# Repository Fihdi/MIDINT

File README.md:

# 6hp MIDI Interface (work in progress)

MIDINT is an eight channel MIDI interface in 6hp. Take a standard DIN-5 MIDI cable connected to your favorite DAW or MIDI gear and control up to eight Gate, Trigger and CV channels. Trimmers on the back of the module allow for precise V/Oct tuning. The CV outputs can thus control oscillators and filters without the need for an external quantizer.

Selecting a channel with the "SELECT" encoder and pressing it will switch it between a trigger or gate output.

# Features

- 4 Gate or Trigger outputs
- 4 CV outputs (Can also be used as Gate or Trigger outputs)
- Extension of up to three modules.

# Extension 

Its possible to daisy-chain up to three extension modules to one main module and expand your interface system to a maximum of 32 Gate/Trigger/CV channels. To connect extension module(s) to a main module:

WARNING: Do NOT connect main modules together!

- Turn your modular synthesizer off
- Take an extension module(s) and change the jumper from "MAIN" to "EXT".
- Add jumpers to "EXT1" and "EXT2" to configure the MIDI channels (see table below)
- Connect the extension module(s) to a main module or another extension module in the chain with a wire underneath the power connector.
- Connect each module(s) to power
- Turn your modular synthesizer on

By connecting a MIDI cable into the main module the MIDI data is shared between all modules. The extension modules are addressed by the jumper settings EXT1 and EXT2:

//TODO: Add address table

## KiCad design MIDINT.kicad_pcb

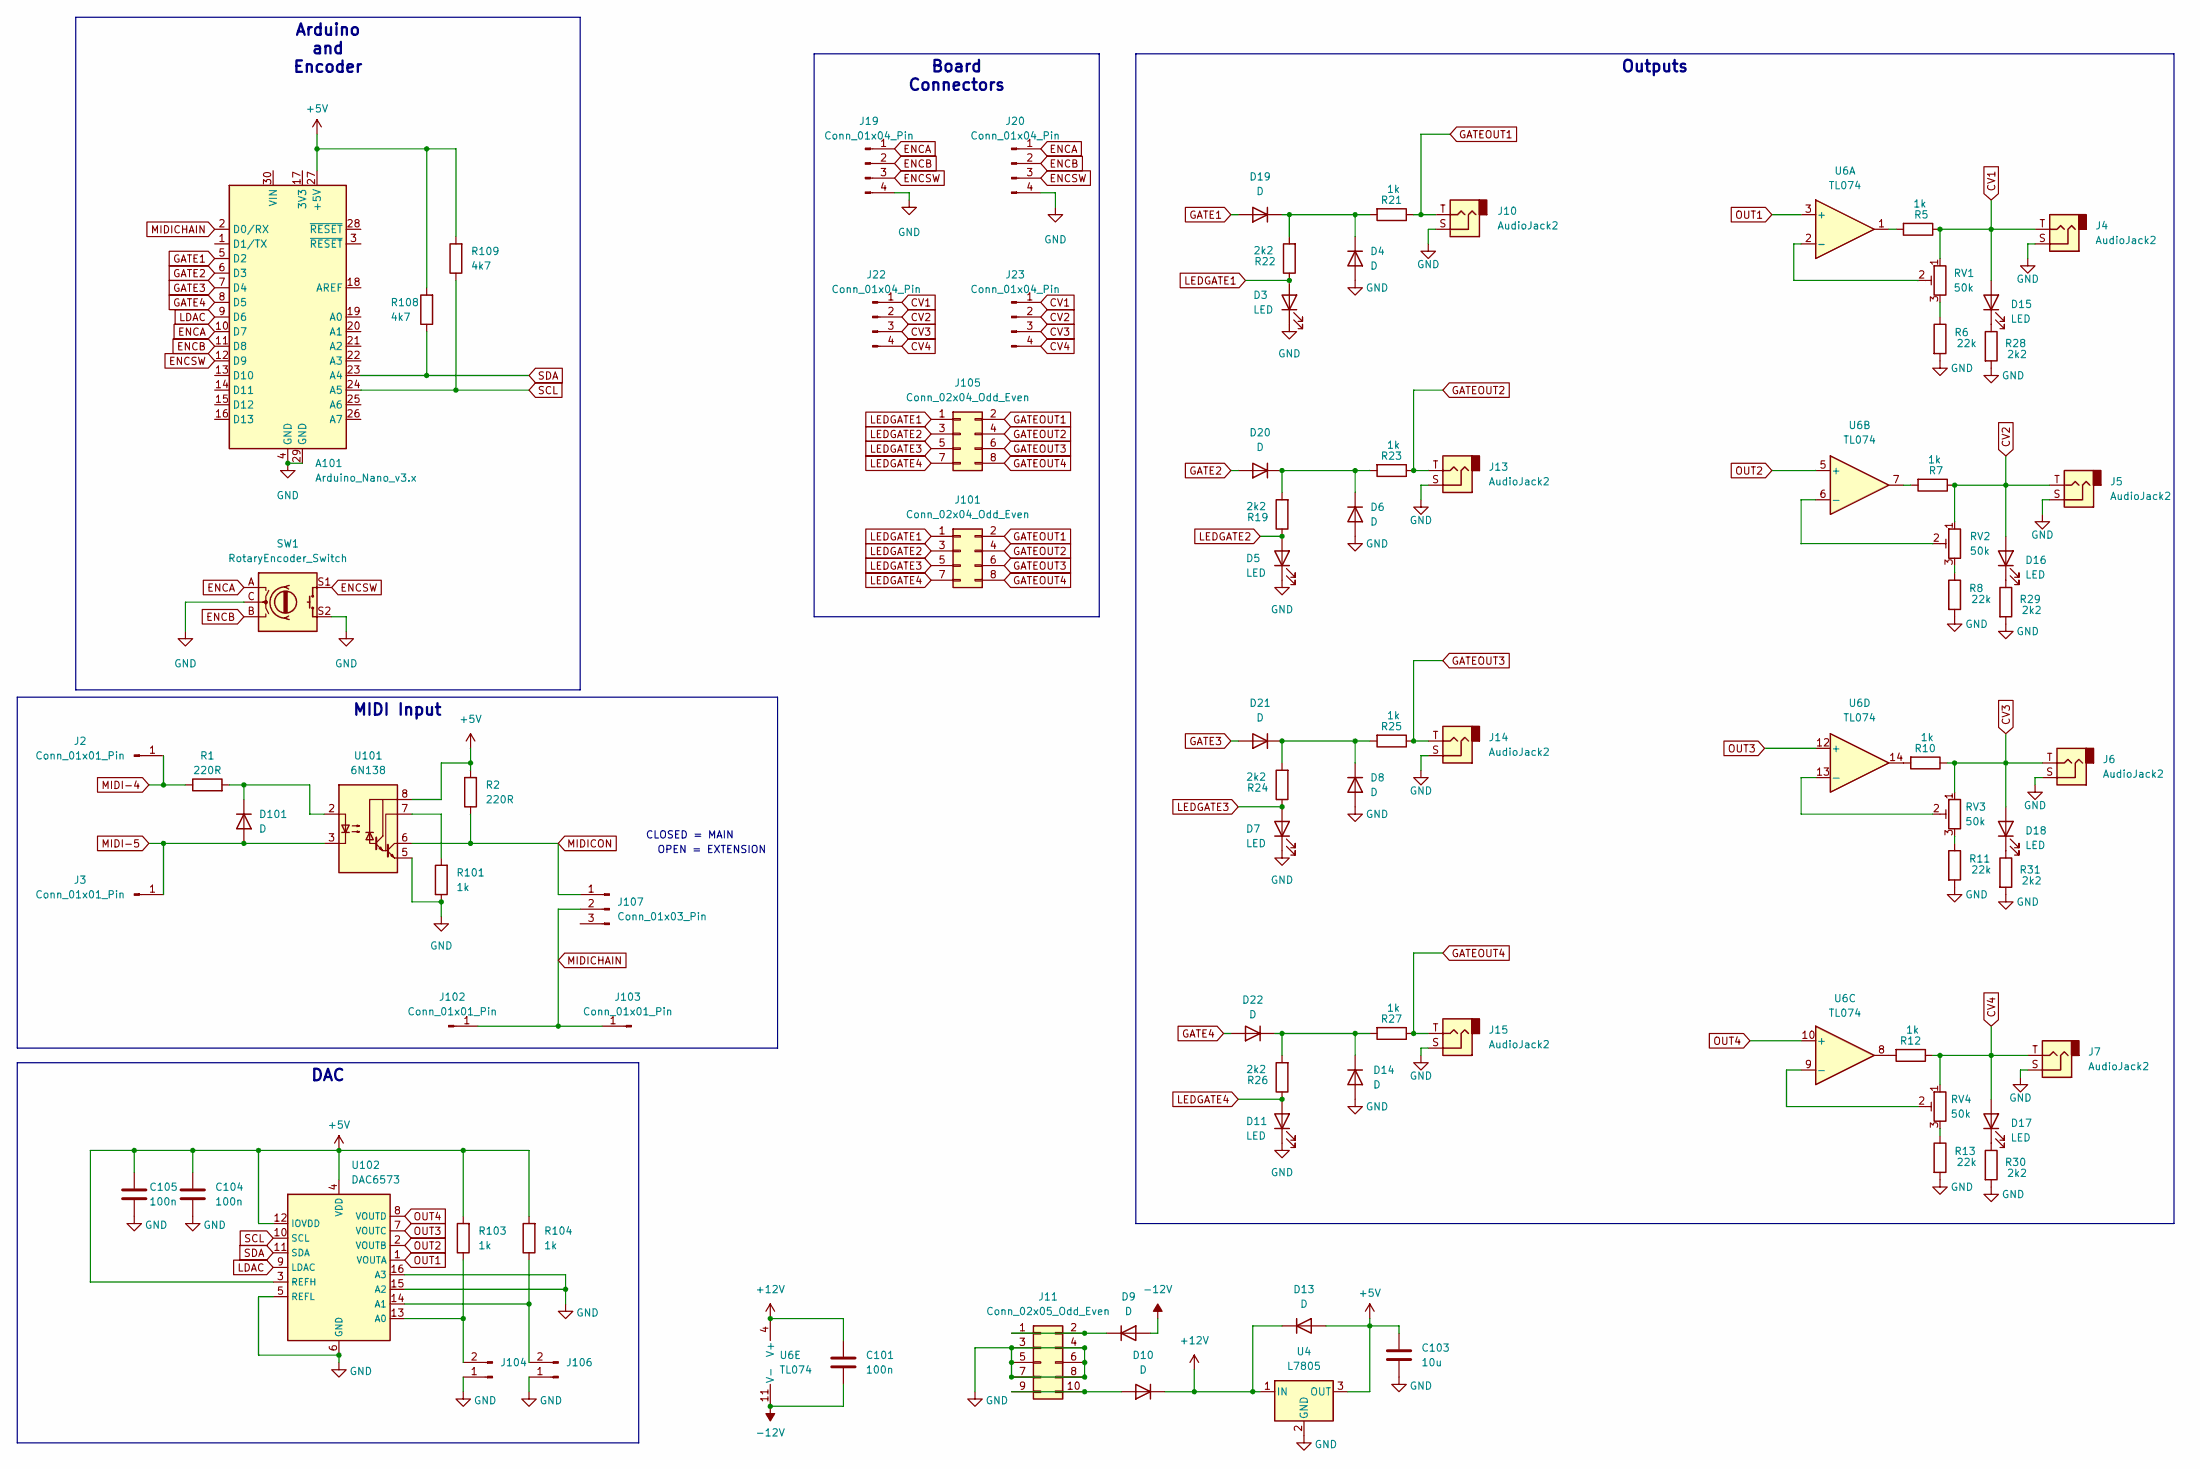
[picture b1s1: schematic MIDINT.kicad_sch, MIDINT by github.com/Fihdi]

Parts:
A101: Arduino_Nano_v3.x; Arduino_Nano
C101, C104, C105: 100n; C_1206_3216Metric
C103: 10u; C_1206_3216Metric
D3, D5, D7, D11, D15, D16, D17, D18: LED; LED_D3.0mm
D4, D6, D8, D9, D10, D13, D14, D19, D20, D21, D22, D101: D; D_SOD-323_HandSoldering
J2, J3, J102, J103: Conn_01x01_Pin; PinHeader_1x01_P2.54mm_Vertical
J4, J5, J6, J7, J10, J13, J14, J15: AudioJack2; MonoTRS
J11: Conn_02x05_Odd_Even; IDC-Header_2x05_P2.54mm_Vertical
J19, J20, J22, J23: Conn_01x04_Pin; PinHeader_1x04_P2.54mm_Vertical
J101, J105: Conn_02x04_Odd_Even; PinHeader_2x04_P2.54mm_Vertical
J104, J106: Conn_01x02_Pin; PinHeader_1x02_P2.54mm_Vertical
J107: Conn_01x03_Pin; PinHeader_1x03_P2.54mm_Vertical
R1, R2: 220R; R_1206_3216Metric
R5, R7, R10, R12, R21, R23, R25, R27, R101, R103, R104: 1k; R_1206_3216Metric
R6, R8, R11, R13: 22k; R_1206_3216Metric
R19, R22, R24, R26, R28, R29, R30, R31: 2k2; R_1206_3216Metric
R108, R109: 4k7; R_1206_3216Metric
RV1, RV2, RV3, RV4: 50k; Potentiometer_Bourns_3296W_Vertical
SW1: RotaryEncoder_Switch; RotaryEncoder_Alps_EC12E-Switch_Vertical_H20mm
U4: L7805; SOT-223
U6: TL074; SOIC-14_3.9x8.7mm_P1.27mm
U101: 6N138; DIP-8_W7.62mm
U102: DAC6573; TSSOP-16_4.4x5mm_P0.65mm

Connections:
+5V: A101.27 (+5V), C103.1, C104.1, C105.1, D13.2 (A), R2.2, R103.2, R104.2, R108.2, R109.2, U4.3 (OUT), U101.8 (VCC), U102.3 (REFH), U102.4 (VDD), U102.12 (IOVDD)
+12V: C101.1, D10.1 (K), D13.1 (K), U4.1 (IN), U6.4 (V+)
-12V: C101.2, D9.2 (A), U6.11 (V-)
CV1: D15.2 (A), J4.T, J22.1, J23.1, R5.1, RV1.1
CV2: D16.2 (A), J5.T, J22.2, J23.2, R7.1, RV2.1
CV3: D18.2 (A), J6.T, J22.3, J23.3, R10.1, RV3.1
CV4: D17.2 (A), J7.T, J22.4, J23.4, R12.1, RV4.1
ENCA: A101.10 (D7), J19.1, J20.1, SW1.A
ENCB: A101.11 (D8), J19.2, J20.2, SW1.B
ENCSW: A101.12 (D9), J19.3, J20.3, SW1.S1
GATE1: A101.5 (D2), D19.2 (A)
GATE2: A101.6 (D3), D20.2 (A)
GATE3: A101.7 (D4), D21.2 (A)
GATE4: A101.8 (D5), D22.2 (A)
GATEOUT1: J10.T, J101.2, J105.2, R21.1
GATEOUT2: J13.T, J101.4, J105.4, R23.1
GATEOUT3: J14.T, J101.6, J105.6, R25.1
GATEOUT4: J15.T, J101.8, J105.8, R27.1
GND: A101.4 (GND), A101.29 (GND), C103.2, C104.2, C105.2, D3.1 (K), D4.2 (A), D5.1 (K), D6.2 (A), D7.1 (K), D8.2 (A), D11.1 (K), D14.2 (A), J4.S, J5.S, J6.S, J7.S, J10.S, J11.3, J11.4, J11.5, J11.6, J11.7, J11.8, J13.S, J14.S, J15.S, J19.4, J20.4, J104.1, J106.1, R6.2, R8.2, R11.2, R13.2, R28.2, R29.2, R30.2, R31.2, R101.1, SW1.C, SW1.S2, U4.2 (GND), U101.5 (GND), U102.5 (REFL), U102.6 (GND), U102.15 (A2), U102.16 (A3)
LDAC: A101.9 (D6), U102.9 (LDAC)
LEDGATE1: D3.2 (A), J101.1, J105.1, R22.1
LEDGATE2: D5.2 (A), J101.3, J105.3, R19.1
LEDGATE3: D7.2 (A), J101.5, J105.5, R24.1
LEDGATE4: D11.2 (A), J101.7, J105.7, R26.1
MIDI-4: J2.1, R1.1
MIDI-5: D101.2 (A), J3.1, U101.3 (C2)
MIDICHAIN: A101.2 (D0/RX), J102.1, J103.1, J107.2
MIDICON: J107.1, R2.1, U101.6 (VO2)
unnamed: D9.1 (K), J11.1, J11.2
unnamed: D10.2 (A), J11.9, J11.10
unnamed: D14.1 (K), D22.1 (K), R26.2, R27.2
unnamed: D15.1 (K), R28.1
unnamed: D16.1 (K), R29.1
unnamed: D17.1 (K), R30.1
unnamed: D18.1 (K), R31.1
unnamed: D4.1 (K), D19.1 (K), R21.2, R22.2
unnamed: D6.1 (K), D20.1 (K), R19.2, R23.2
unnamed: D8.1 (K), D21.1 (K), R24.2, R25.2
unnamed: D101.1 (K), R1.2, U101.2 (C1)
unnamed: J104.2, R103.1, U102.13 (A0)
unnamed: J106.2, R104.1, U102.14 (A1)
unnamed: R5.2, U6.1
unnamed: R6.1, RV1.3
unnamed: R7.2, U6.7
unnamed: R8.1, RV2.3
unnamed: R10.2, U6.14
unnamed: R11.1, RV3.3
unnamed: R12.2, U6.8
unnamed: R13.1, RV4.3
unnamed: RV1.2, U6.2 (-)
unnamed: RV2.2, U6.6 (-)
unnamed: RV4.2, U6.9 (-)
unnamed: RV3.2, U6.13 (-)
unnamed: R101.2, U101.7 (VO1)
OUT1: U6.3 (+), U102.1 (VOUTA)
OUT2: U6.5 (+), U102.2 (VOUTB)
OUT3: U6.12 (+), U102.7 (VOUTC)
OUT4: U6.10 (+), U102.8 (VOUTD)
SCL: A101.24 (A5), R109.1, U102.10 (SCL)
SDA: A101.23 (A4), R108.1, U102.11 (SDA)

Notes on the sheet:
CLOSED = MAIN
OPEN = EXTENSION
MIDI Input
DAC
Board Connectors
Arduino and Encoder
Outputs

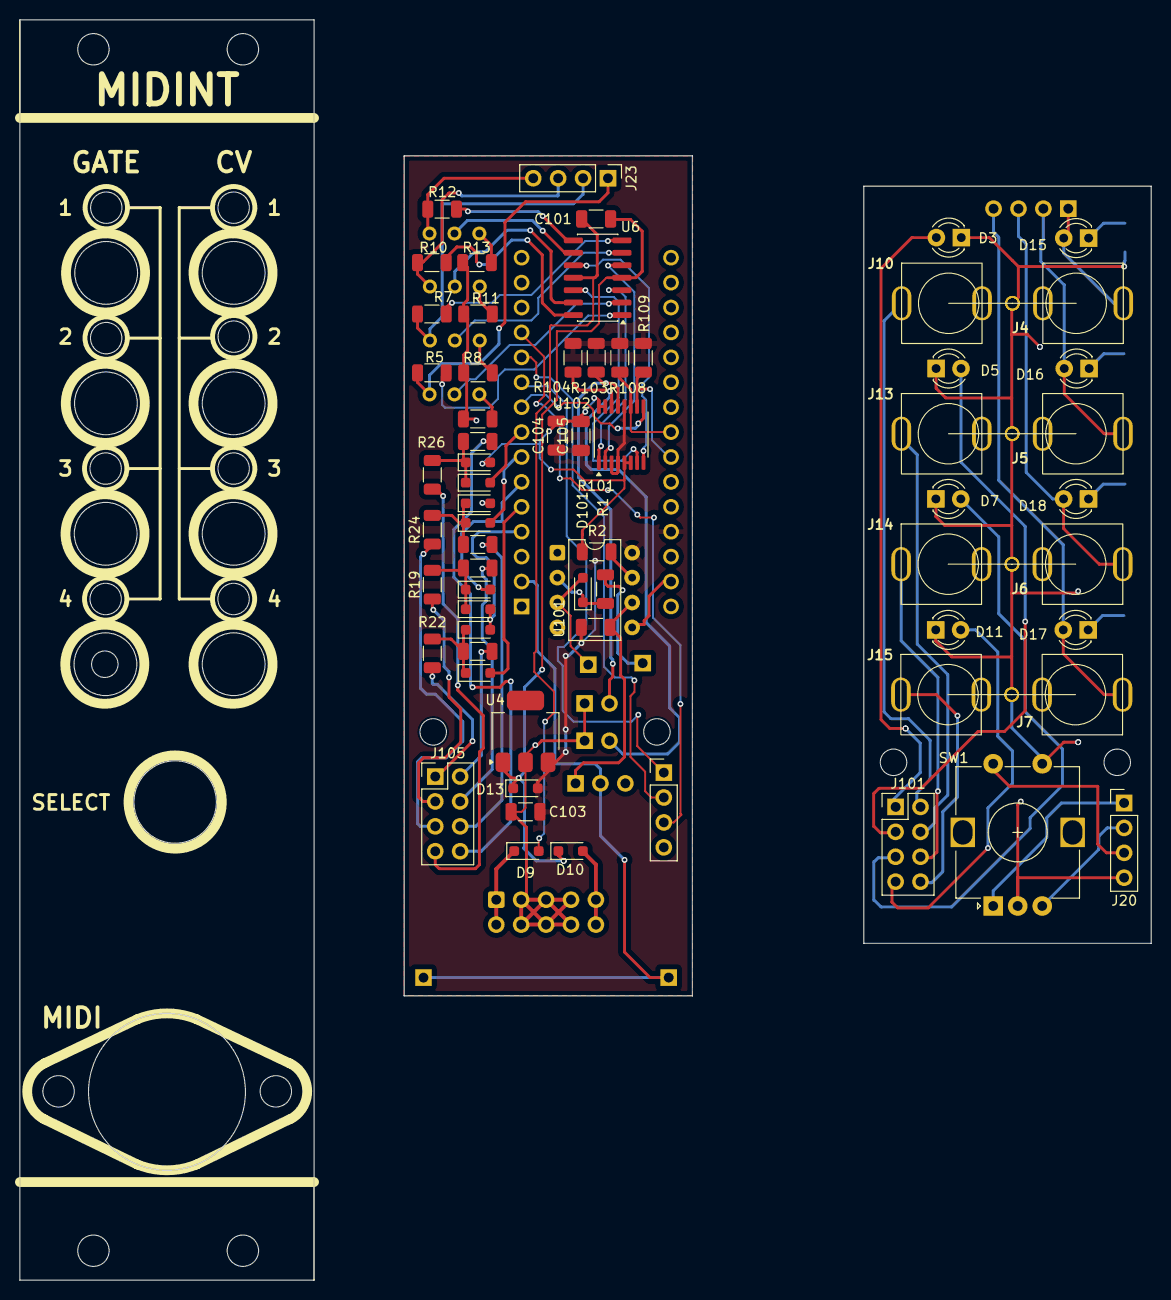
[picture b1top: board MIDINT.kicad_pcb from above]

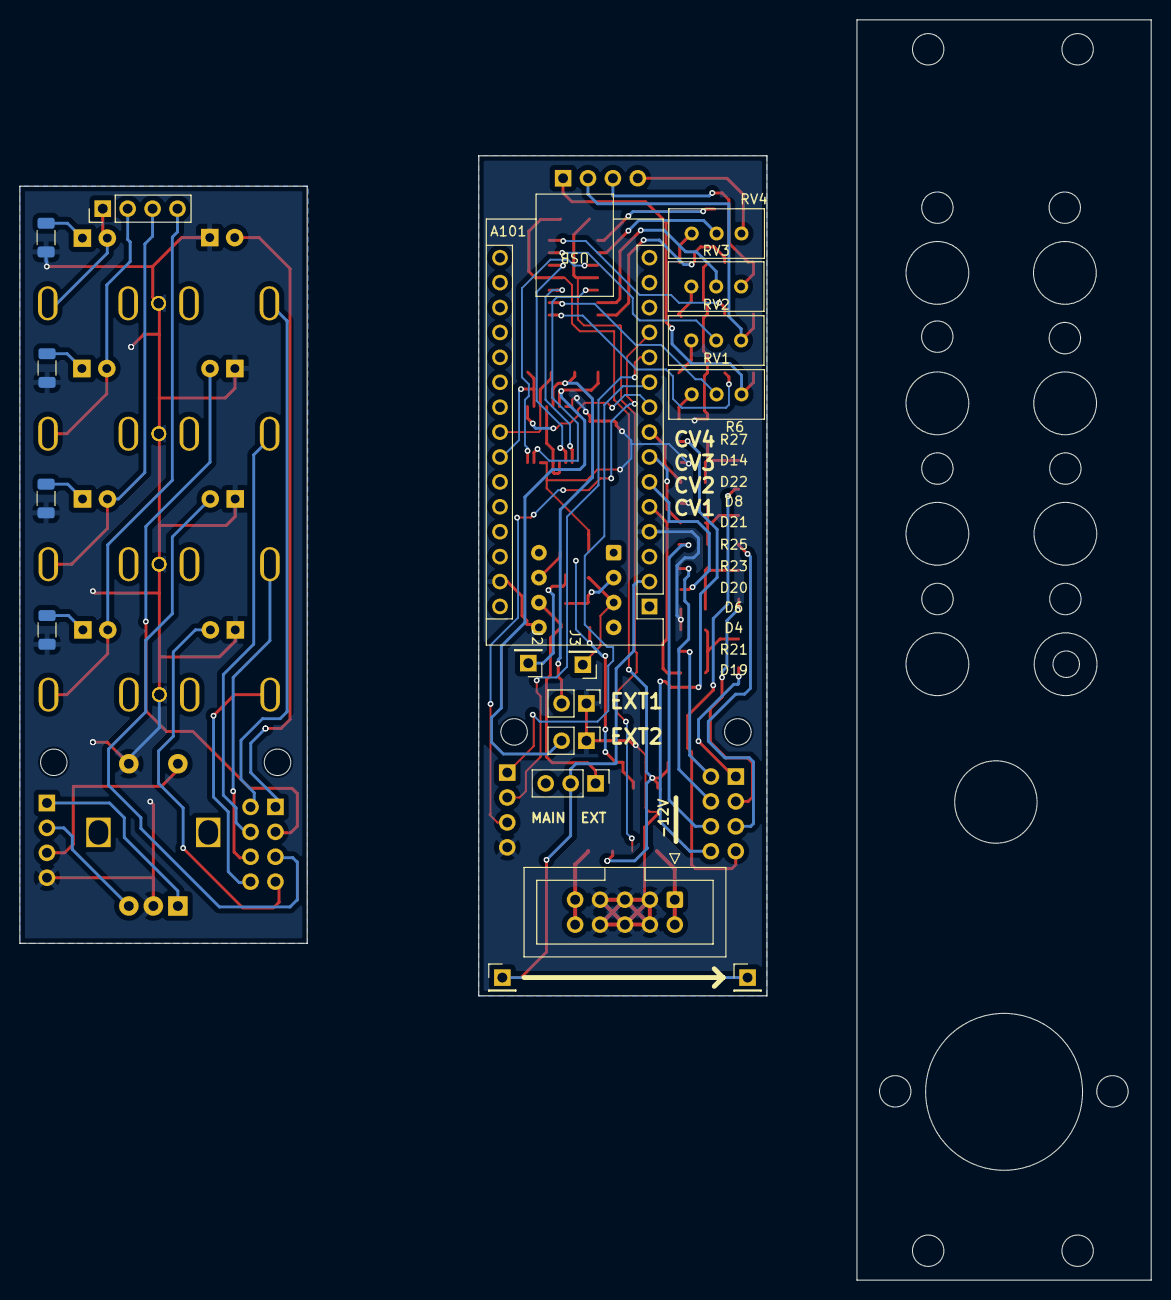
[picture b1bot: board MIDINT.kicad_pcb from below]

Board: 2 copper layers, 115.4 x 128.5 mm, 83 parts (18 on the bottom side), 60 nets.

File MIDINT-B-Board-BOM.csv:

"Reference","Qty","Value","DNP","Exclude from BOM","Exclude from Board","Footprint","Datasheet"
"A101","1","Arduino_Nano_v3.x","","","","Module:Arduino_Nano","http://www.mouser.com/pdfdocs/Gravitech_Arduino_Nano3_0.pdf"
"C101,C104,C105","3","100n","","","","Capacitor_SMD:C_1206_3216Metric","~"
"C103","1","10u","","","","Capacitor_SMD:C_1206_3216Metric","~"
"D4,D6,D8,D9,D10,D13,D14,D19,D20,D21,D22,D101","12","D","","","","Diode_SMD:D_SOD-323_HandSoldering","~"
"J2,J3,J102,J103","4","Conn_01x01_Pin","","","","Connector_PinHeader_2.54mm:PinHeader_1x01_P2.54mm_Vertical","~"
"J11","1","Conn_02x05_Odd_Even","","","","Connector_IDC:IDC-Header_2x05_P2.54mm_Vertical","~"
"J19,J23","2","Conn_01x04_Pin","","","","Connector_PinHeader_2.54mm:PinHeader_1x04_P2.54mm_Vertical","~"
"J104,J106","2","Conn_01x02_Pin","","","","Connector_PinHeader_2.54mm:PinHeader_1x02_P2.54mm_Vertical","~"
"J105","1","Conn_02x04_Odd_Even","","","","Connector_PinHeader_2.54mm:PinHeader_2x04_P2.54mm_Vertical","~"
"J107","1","Conn_01x03_Pin","","","","Connector_PinHeader_2.54mm:PinHeader_1x03_P2.54mm_Vertical","~"
"R1,R2","2","220R","","","","Resistor_SMD:R_1206_3216Metric","~"
"R5,R7,R10,R12,R21,R23,R25,R27,R101,R103,R104","11","1k","","","","Resistor_SMD:R_1206_3216Metric","~"
"R6,R8,R11,R13","4","22k","","","","Resistor_SMD:R_1206_3216Metric","~"
"R19,R22,R24,R26","4","2k2","","","","Resistor_SMD:R_1206_3216Metric","~"
"R108,R109","2","4k7","","","","Resistor_SMD:R_1206_3216Metric","~"
"RV1,RV2,RV3,RV4","4","50k","","","","Potentiometer_THT:Potentiometer_Bourns_3296W_Vertical","~"
"U4","1","L7805","","","","Package_TO_SOT_SMD:SOT-223","http://www.st.com/content/ccc/resource/technical/document/da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"
"U6","1","TL074","","","","Package_SO:SOIC-14_3.9x8.7mm_P1.27mm","http://www.ti.com/lit/ds/symlink/tl071.pdf"
"U101","1","6N138","","","","Package_DIP:DIP-8_W7.62mm","http://www.onsemi.com/pub/Collateral/HCPL2731-D.pdf"
"U102","1","DAC6573","","","","Package_SO:TSSOP-16_4.4x5mm_P0.65mm",""
